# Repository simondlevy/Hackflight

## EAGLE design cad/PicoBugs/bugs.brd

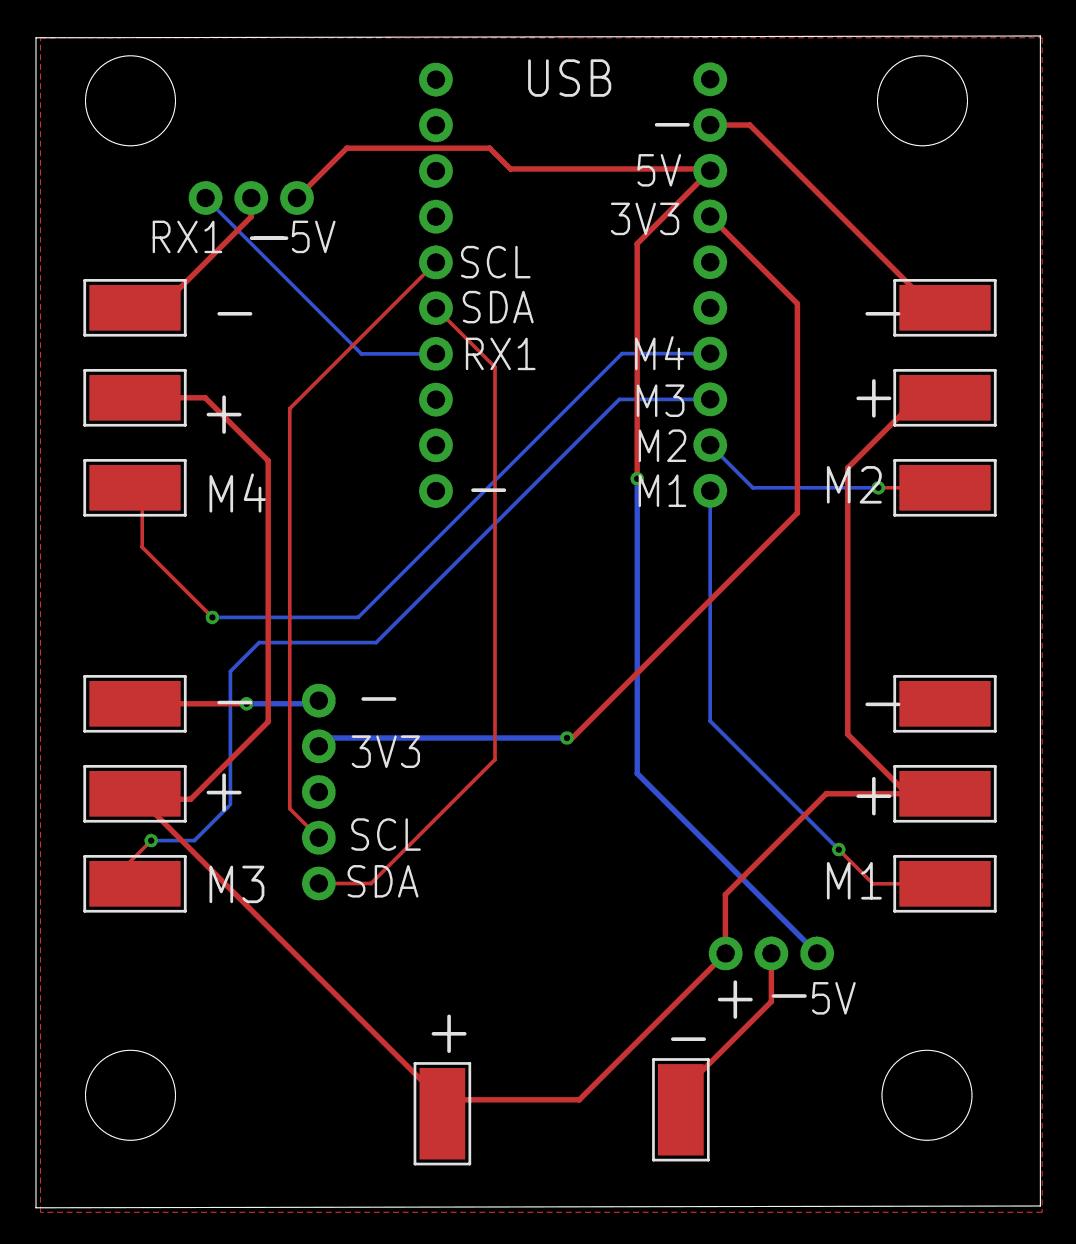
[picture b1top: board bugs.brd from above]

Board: 2 copper layers, 55.8 x 65.1 mm, 19 parts (1 on the bottom side), 11 nets.

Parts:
GND, GND1, GND2, GND3, GND4: WIREPADSMD5-2,5; 5-2,5
J1, J2: 1X10_NO_SILK
J3, J5: 1X03_NO_SILK
J4: 1X05_NO_SILK
M1, M2, M3, M4: WIREPADSMD5-2,5; 5-2,5
VBAT, VBAT1, VBAT2, VBAT3, VBAT4: WIREPADSMD5-2,5; 5-2,5

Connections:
3V3: J1.4, J4.4
5V: J1.3, J3.1, J5.1
GND: GND.1, GND1.1, GND2.1, GND3.1, GND4.1, J1.2, J2.10, J3.2, J4.5, J5.2
M1: J1.10, M1.1
M2: J1.9, M2.1
M3: J1.8, M3.1
M4: J1.7, M4.1
RX1: J2.7, J5.3
SCL: J2.5, J4.2
SDA: J2.6, J4.1
VBAT: J3.3, VBAT.1, VBAT1.1, VBAT2.1, VBAT3.1, VBAT4.1

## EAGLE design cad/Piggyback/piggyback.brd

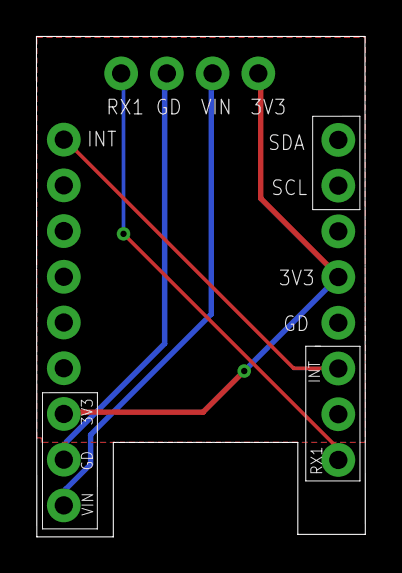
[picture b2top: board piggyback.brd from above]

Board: 2 copper layers, 18.3 x 27.8 mm, 3 parts (0 on the bottom side), 5 nets.

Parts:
J1: 1X09_NO_SILK
J2: 1X08_NO_SILK
J3: 1X04_NO_SILK

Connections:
3V3: J1.3, J2.5, J3.1
GND: J1.2, J2.4, J3.3
INT: J1.9, J2.3
RX1: J2.1, J3.4
VIN: J1.1, J3.2

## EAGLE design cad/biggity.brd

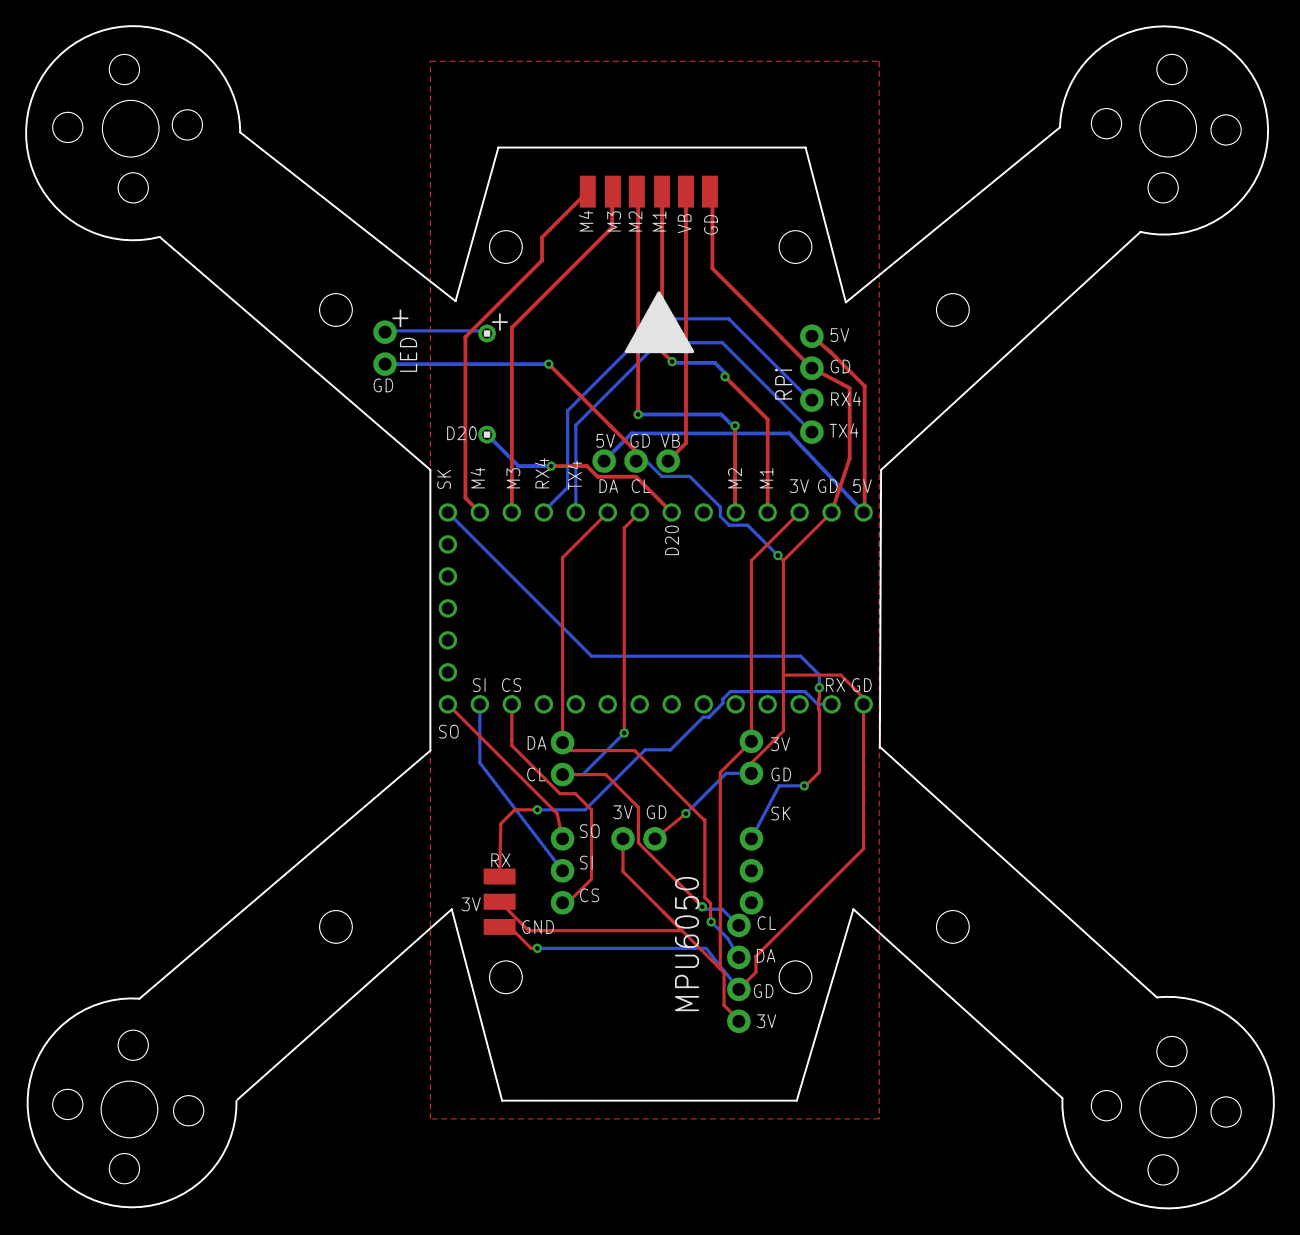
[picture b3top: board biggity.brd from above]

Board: 2 copper layers, 99.1 x 93.9 mm, 21 parts (1 on the bottom side), 19 nets.

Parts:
3V: SMD1,27-2,54
GND: SMD1,27-2,54
LED: 1X02_NO_SILK
LED_R_IN: 1X1
LED_R_OUT: 1X1
MPU6050: 1X04_NO_SILK
PAD1, PAD2, PAD3, PAD4, PAD5, PAD6: SMD1,27-2,54
PMW3901_1, PMW3901_2: 1X03_NO_SILK
PMW3901_3: 1X02_NO_SILK
REG: 1X03_NO_SILK
RPI: 1X04_NO_SILK
RX: SMD1,27-2,54
U$1: TEENSY_4.0
VL53L1_1, VL53L1_2: 1X02_NO_SILK

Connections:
3V3: 3V.1, MPU6050.1, PMW3901_3.1, U$1.3V3_LO, VL53L1_1.2
5V: REG.1, RPI.4, U$1.VIN
CS: PMW3901_2.3, U$1.10/CS
GND: GND.1, LED.1, MPU6050.2, PAD1.1, PMW3901_3.2, REG.2, RPI.3, U$1.GND, U$1.GND2, VL53L1_1.1
LED_R_IN: LED_R_IN.1, U$1.20/A6
LED_R_OUT: LED.2, LED_R_OUT.1
M1: PAD3.1, U$1.23/A9
M2: PAD4.1, U$1.22/A8
M3: PAD5.1, U$1.15/A1
M4: PAD6.1, U$1.14/A0
MISO: PMW3901_2.1, U$1.12/MISO
MOSI: PMW3901_2.2, U$1.11/MOSI
RX: RX.1, U$1.0/RX
RX4: RPI.2, U$1.16/A2
SCK: PMW3901_1.1, U$1.13/SCK
SCL: MPU6050.4, U$1.19/A5/SCL, VL53L1_2.1
SDA: MPU6050.3, U$1.18/A4/SDA, VL53L1_2.2
TX4: RPI.1, U$1.17/A3
VBAT: PAD2.1, REG.3

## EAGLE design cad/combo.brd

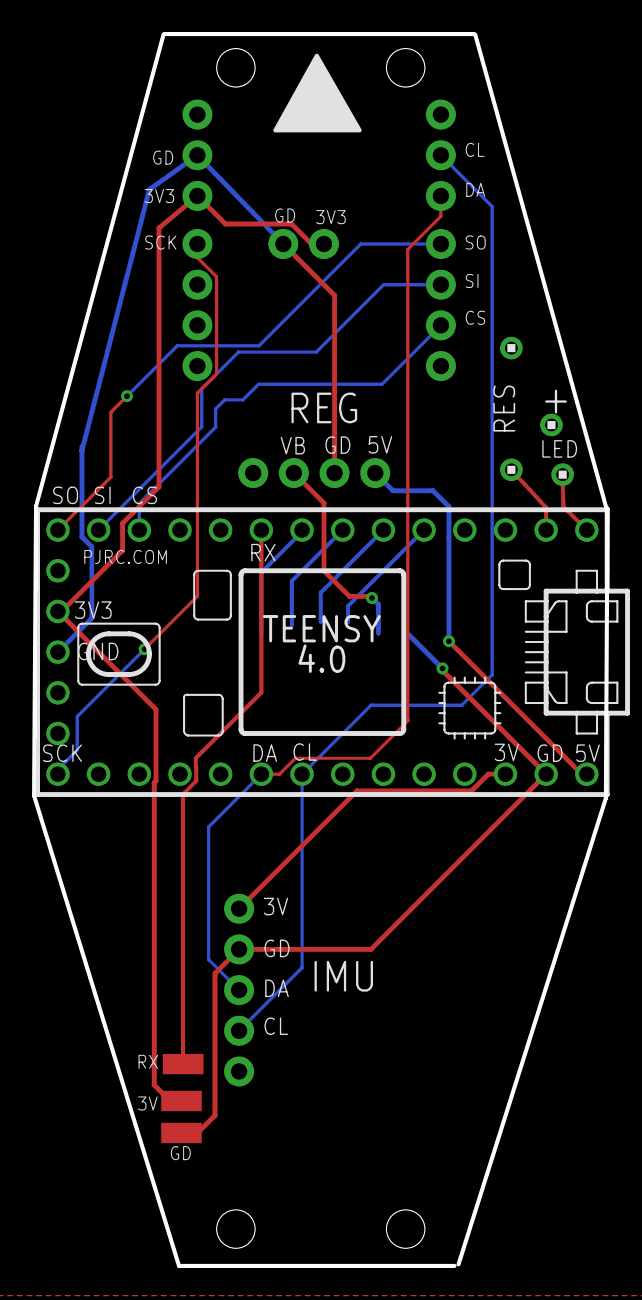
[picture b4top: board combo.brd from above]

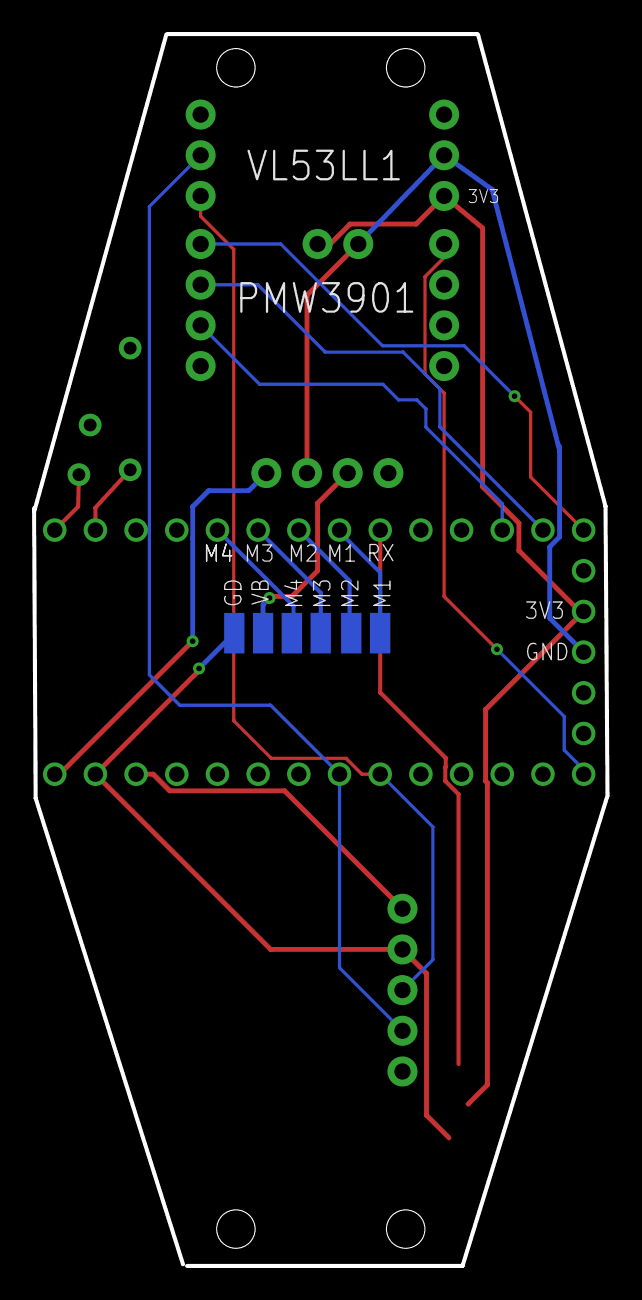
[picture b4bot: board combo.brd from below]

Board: 2 copper layers, 35.8 x 76.9 mm, 21 parts (6 on the bottom side), 18 nets.

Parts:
3V: SMD1,27-2,54
GD: SMD1,27-2,54
GND: SMD1,27-2,54
M1, M2, M3, M4: SMD1,27-2,54
MPU6050: 1X05_NO_SILK
PMW1, PMW2: 1X04_NO_SILK
PMW3: 1X02_NO_SILK
REG: 1X04_NO_SILK
RX: SMD1,27-2,54
U$1: TEENSY_4.0
U$3, U$4, U$6, U$7: 1X1
VBAT: SMD1,27-2,54
VL1, VL2: 1X03_NO_SILK

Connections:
3V3: 3V.1, MPU6050.1, PMW3.1, U$1.3V3_LN, U$1.3V3_LO, VL2.1
5V: REG.1, U$1.VIN
CS: PMW2.3, U$1.10/CS
G2: U$1.GND, U$7.1
GND: GD.1, GND.1, MPU6050.2, PMW3.2, REG.2, U$1.GND2, U$1.GND3, VL2.2
LED_R_IN: U$1.0/RX, U$3.1
LED_R_OUT: U$4.1, U$6.1
M1: M1.1, U$1.6
M2: M2.1, U$1.5
M3: M3.1, U$1.4/CANRX
M4: M4.1, U$1.3/CANTX
MISO: PMW2.1, U$1.12/MISO
MOSI: PMW2.2, U$1.11/MOSI
RX: RX.1, U$1.7
SCK: PMW1.1, U$1.13/SCK
SCL: MPU6050.4, U$1.19/A5/SCL, VL1.2
SDA: MPU6050.3, U$1.18/A4/SDA, VL1.1
VBAT: REG.3, VBAT.1

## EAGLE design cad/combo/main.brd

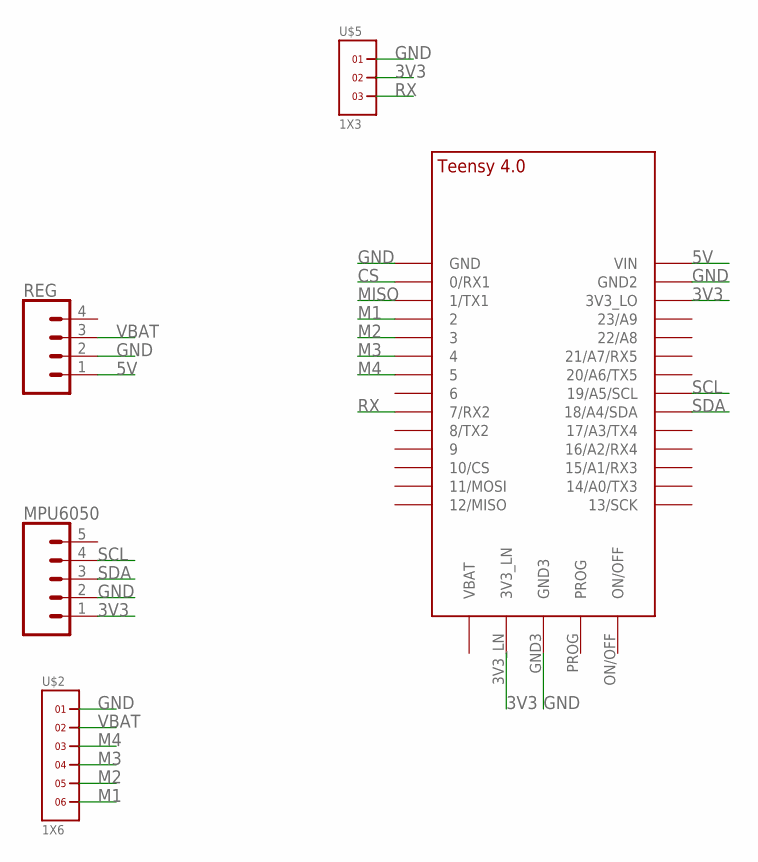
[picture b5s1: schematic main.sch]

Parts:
MPU6050: CONN_05NO_SILK; 1X05_NO_SILK
REG: CONN_041X04_NO_SILK; 1X04_NO_SILK
U$1: TEENSY_4.0
U$2: 1X6
U$5: 1X3

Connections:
3V3: MPU6050.1, U$1.3V3_LN, U$1.3V3_LO, U$5.2
5V: REG.1, U$1.VIN
CS: U$1.0/RX (0/RX1)
GND: MPU6050.2, REG.2, U$1.GND, U$1.GND2, U$1.GND3, U$2.1, U$5.1
M1: U$1.2, U$2.6
M2: U$1.3/CANTX (3), U$2.5
M3: U$1.4/CANRX (4), U$2.4
M4: U$1.5, U$2.3
MISO: U$1.1/TX (1/TX1)
RX: U$1.7 (7/RX2), U$5.3
SCL: MPU6050.4, U$1.19/A5/SCL
SDA: MPU6050.3, U$1.18/A4/SDA
VBAT: REG.3, U$2.2

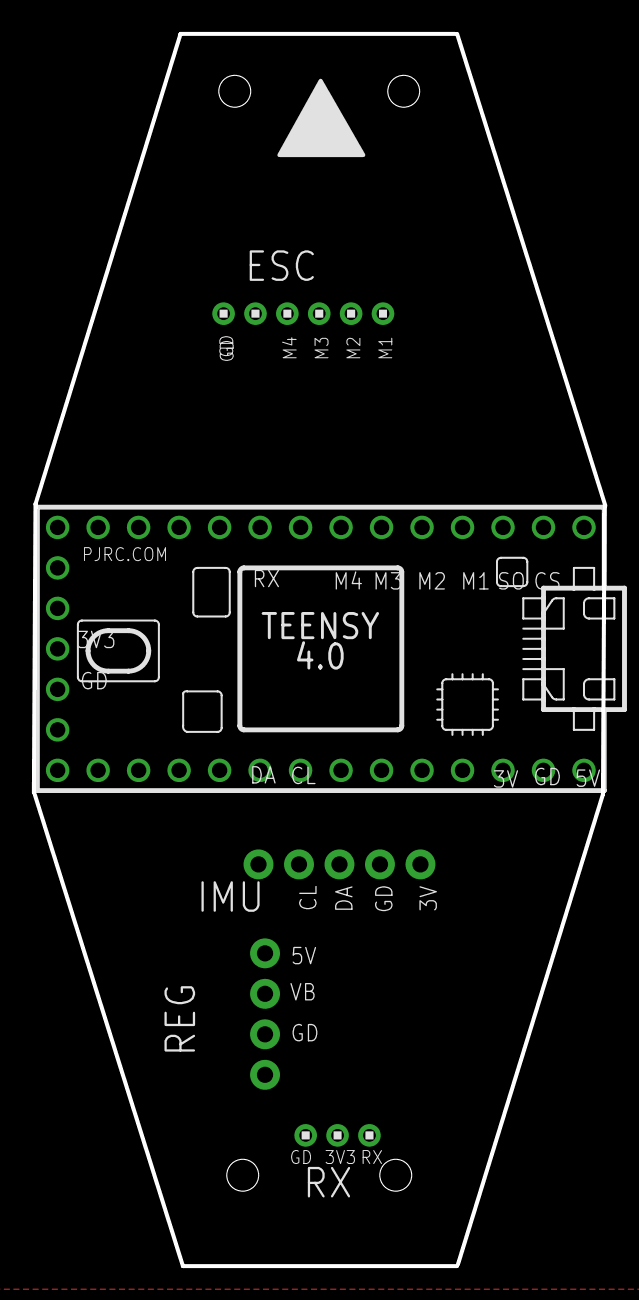
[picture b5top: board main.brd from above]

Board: 2 copper layers, 35.8 x 77.3 mm, 5 parts (0 on the bottom side), 11 nets.

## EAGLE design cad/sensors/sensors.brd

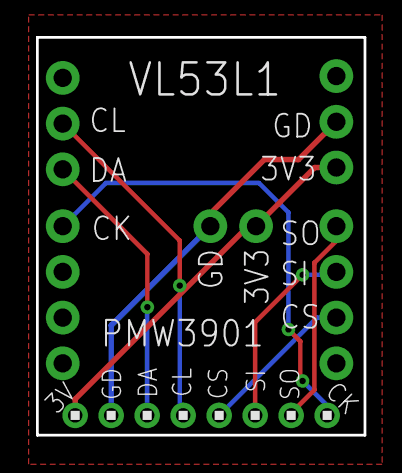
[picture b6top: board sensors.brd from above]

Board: 2 copper layers, 18.2 x 22.1 mm, 6 parts (0 on the bottom side), 8 nets.

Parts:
PMW3091: 1X02_NO_SILK
PMW3901A, PMW3901B: 1X04_NO_SILK
U$1: 1X8
VL53L1A, VL53L1B: 1X03_NO_SILK

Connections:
3V3: PMW3091.2, U$1.8, VL53L1A.3
CS: PMW3901A.3, U$1.4
GND: PMW3091.1, U$1.7, VL53L1A.2
MISO: PMW3901A.1, U$1.2
MOSI: PMW3901A.2, U$1.3
SCK: PMW3901B.1, U$1.1
SCL: U$1.5, VL53L1B.2
SDA: U$1.6, VL53L1B.3

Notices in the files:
parts and their libraries:
SparkFun-Connectors: Licensing: Creative Commons ShareAlike 4.0 International - https://creativecommons.org/licenses/by-sa/4.0
